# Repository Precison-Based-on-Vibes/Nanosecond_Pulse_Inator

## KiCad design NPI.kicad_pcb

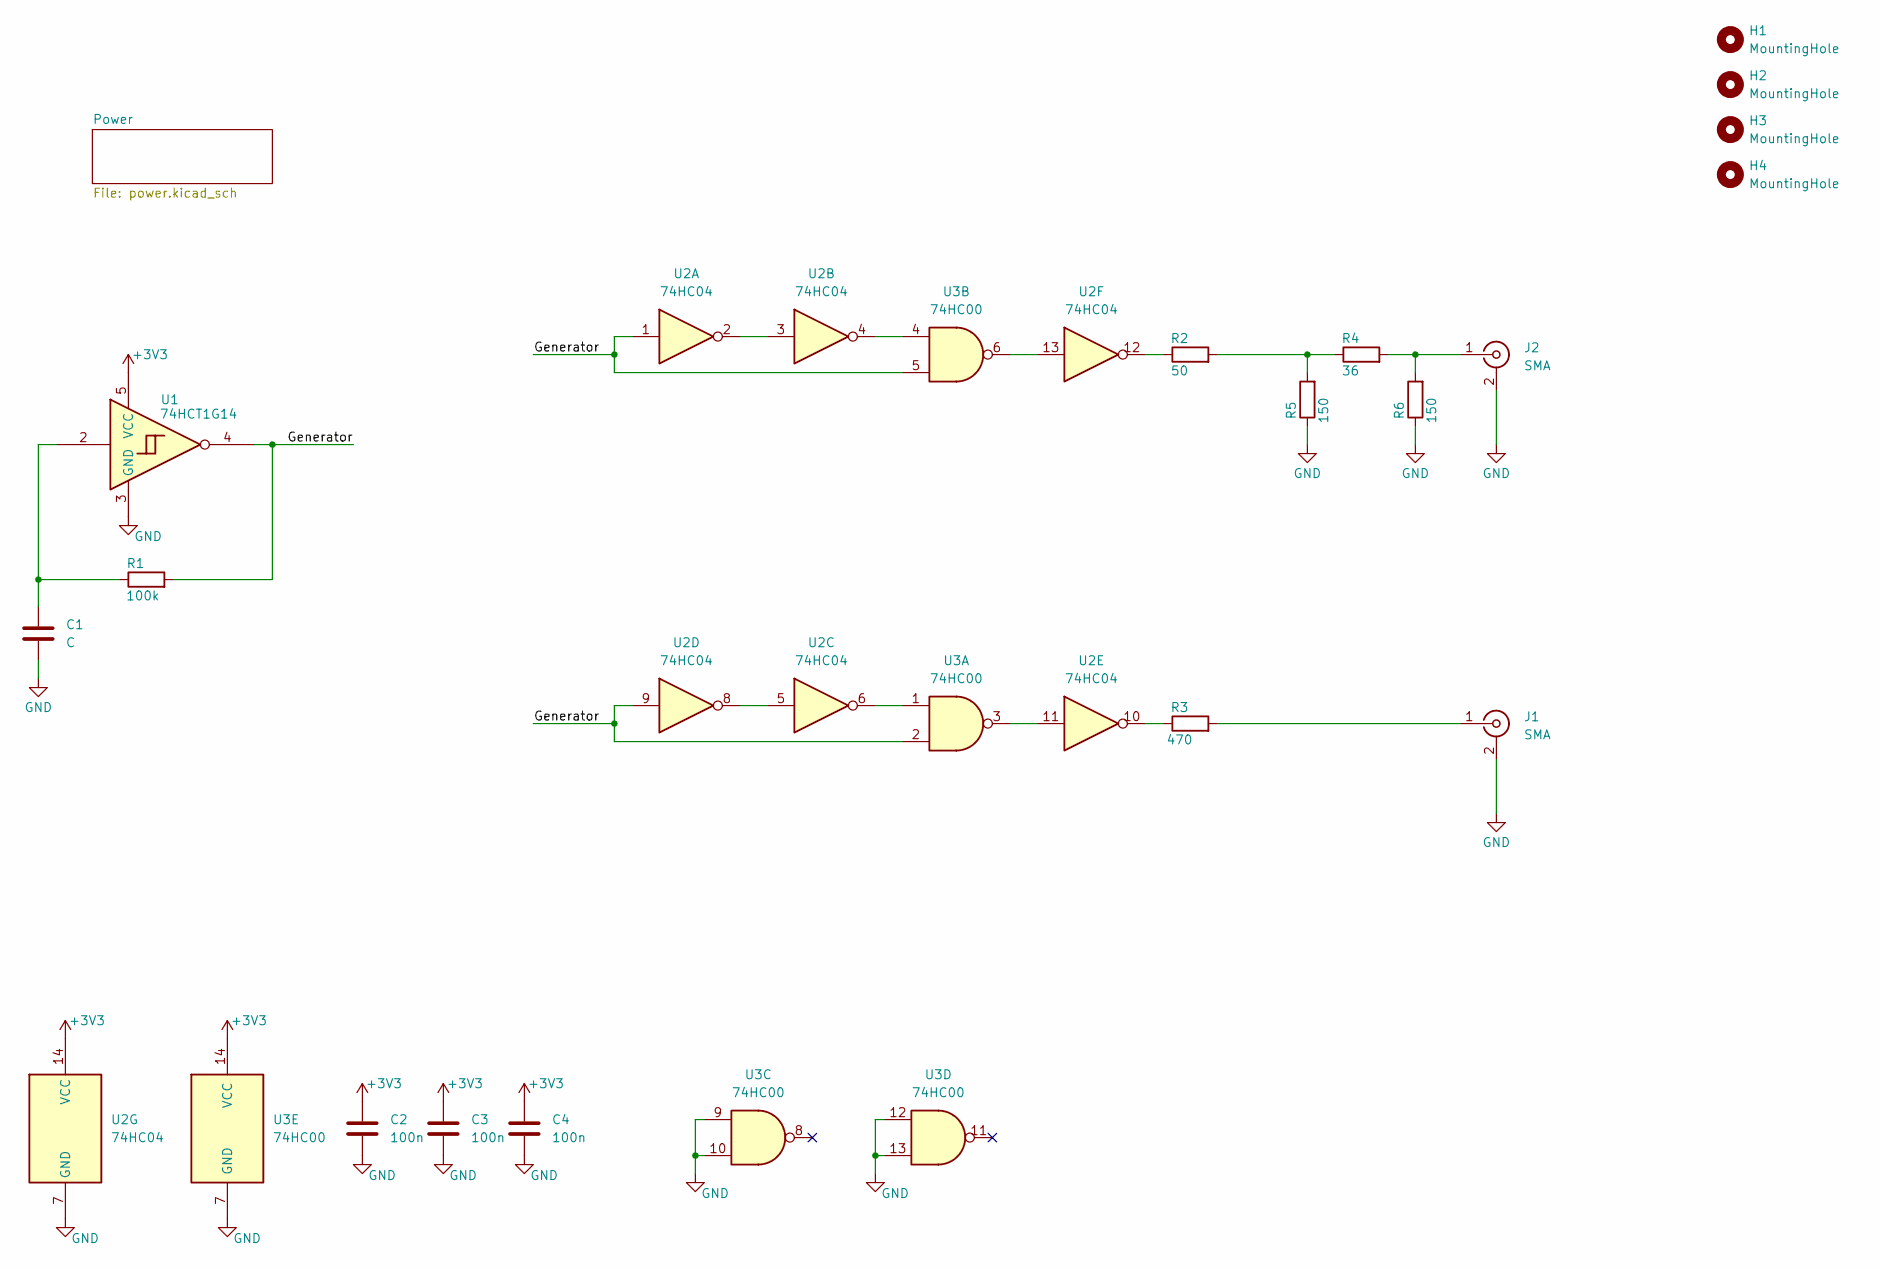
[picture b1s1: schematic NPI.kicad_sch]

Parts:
C1: C; C_0805_2012Metric_Pad1.18x1.45mm_HandSolder
C2, C3, C4: 100n; C_0805_2012Metric_Pad1.18x1.45mm_HandSolder
H1, H2, H3, H4: MountingHole; MountingHole_3.2mm_M3_DIN965
J1, J2: SMA; SMA_Amphenol_132289_EdgeMount
R1: 100k; R_0805_2012Metric_Pad1.20x1.40mm_HandSolder
R2: 50; R_0603_1608Metric_Pad0.98x0.95mm_HandSolder
R3: 470; R_0603_1608Metric_Pad0.98x0.95mm_HandSolder
R4: 36; R_0603_1608Metric_Pad0.98x0.95mm_HandSolder
R5, R6: 150; R_0603_1608Metric_Pad0.98x0.95mm_HandSolder
U1: 74HCT1G14; SOT-353_SC-70-5_Handsoldering
U2: 74HC04; SOIC-14_3.9x8.7mm_P1.27mm
U3: 74HC00; SOIC-14_3.9x8.7mm_P1.27mm

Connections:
+3V3: C2.1, C3.1, C4.1, U1.5 (VCC), U2.14 (VCC), U3.14 (VCC); also elsewhere on the board
/Generator: R1.2, U1.4, U2.1, U2.9, U3.2, U3.5
GND: C1.2, C2.2, C3.2, C4.2, J1.2 (Ext), J2.2 (Ext), R5.1, R6.1, U1.3 (GND), U2.7 (GND), U3.7 (GND), U3.9, U3.10, U3.12, U3.13; also elsewhere on the board
unnamed: C1.1, R1.1, U1.2
unnamed: J1.1 (In), R3.2
unnamed: J2.1 (In), R4.2, R6.2
unnamed: R2.1, U2.12
unnamed: R2.2, R4.1, R5.2
unnamed: R3.1, U2.10
unnamed: U2.2, U2.3
unnamed: U2.4, U3.4
unnamed: U2.5, U2.8
unnamed: U2.6, U3.1
unnamed: U2.11, U3.3
unnamed: U2.13, U3.6

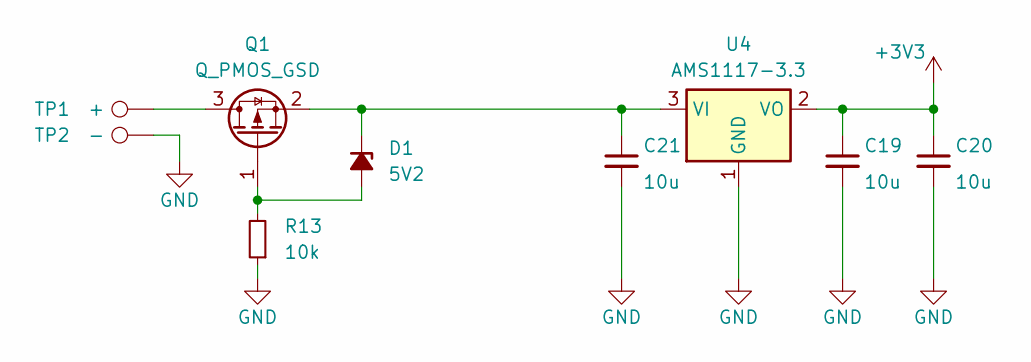
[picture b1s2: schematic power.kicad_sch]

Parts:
C19, C20, C21: 10u; C_0805_2012Metric_Pad1.18x1.45mm_HandSolder
D1: 5V2; D_MiniMELF
Q1: Q_PMOS_GSD; SOT-23_Handsoldering
R13: 10k; R_0805_2012Metric_Pad1.20x1.40mm_HandSolder
TP1: +; TestPoint_Keystone_5019_Miniature
TP2: -; TestPoint_Keystone_5019_Miniature
U4: AMS1117-3.3; SOT-223-3_TabPin2

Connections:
+3V3: C19.1, C20.1, U4.2 (VO); also elsewhere on the board
GND: C19.2, C20.2, C21.2, R13.1, TP2.1, U4.1 (GND); also elsewhere on the board
unnamed: D1.2 (A), Q1.1 (G), R13.2
unnamed: C21.1, D1.1 (K), Q1.2 (S), U4.3 (VI)
unnamed: Q1.3 (D), TP1.1

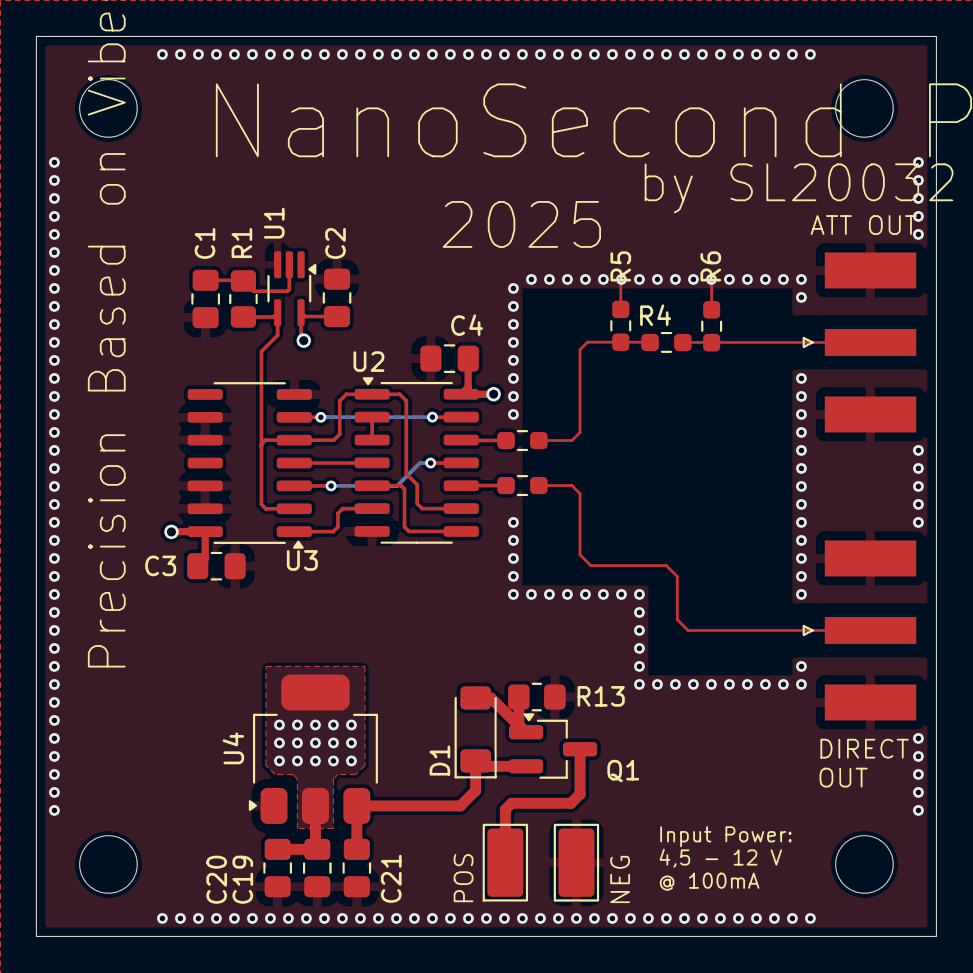
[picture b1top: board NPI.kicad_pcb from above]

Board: 6 copper layers, 50.0 x 50.0 mm, 28 parts (0 on the bottom side), 18 nets.

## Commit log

2025-06-27 Create LICENSE
